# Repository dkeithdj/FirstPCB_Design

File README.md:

# First PCB Design
An attempt to create my first PCB Design

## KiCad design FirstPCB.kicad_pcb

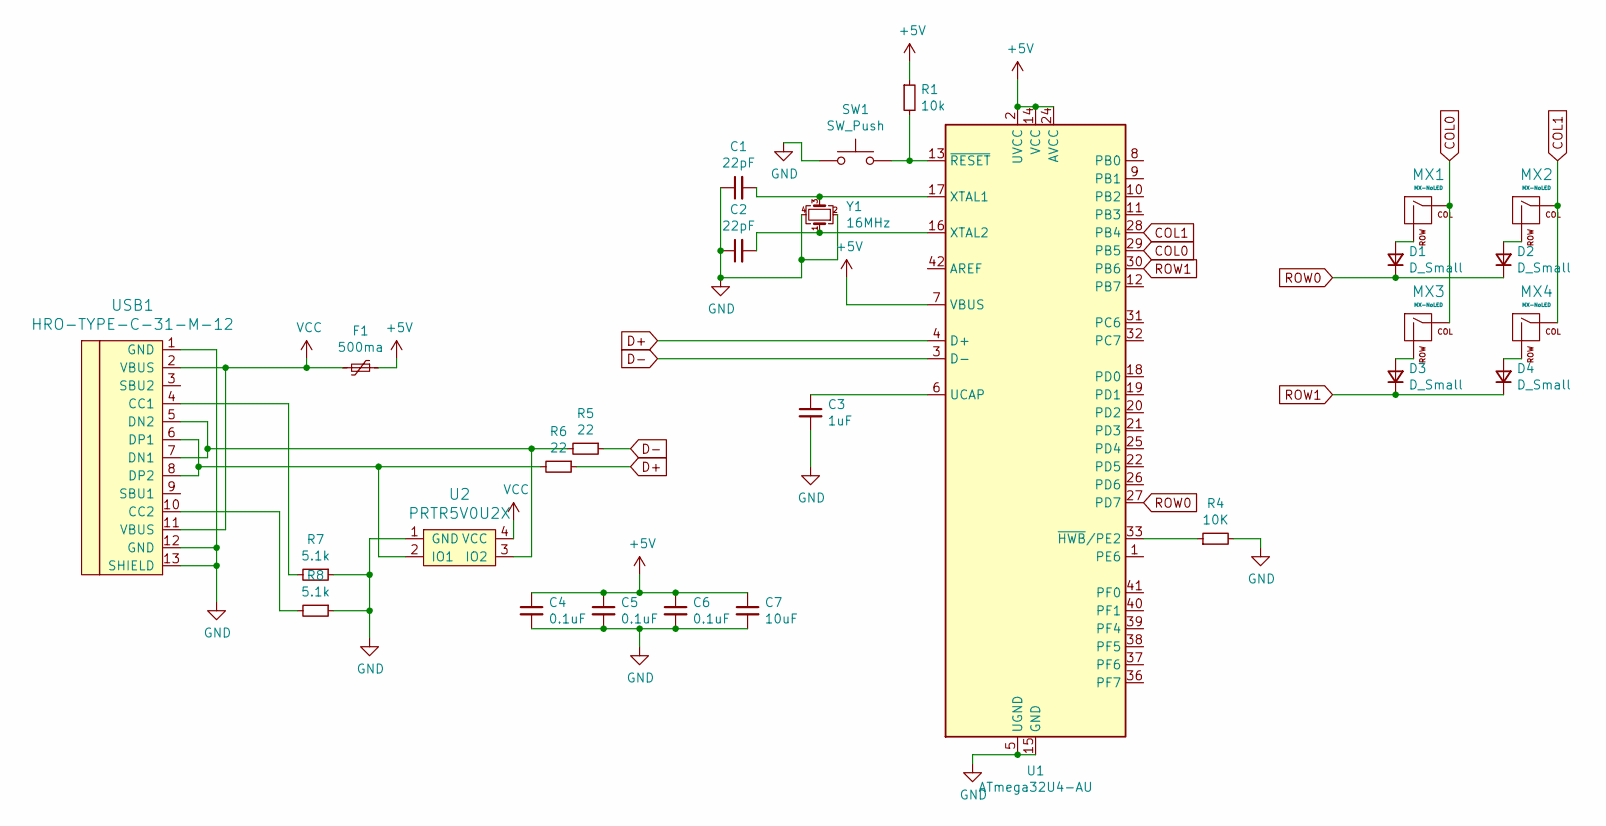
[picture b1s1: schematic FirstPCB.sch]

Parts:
C1, C2: 22pF; C_0805_2012Metric
C3: 1uF; C_0805_2012Metric
C4, C5, C6: 0.1uF; C_0805_2012Metric
C7: 10uF; C_0805_2012Metric
D1, D2, D3, D4: D_Small; D_SOD-123
F1: 500ma; Fuse_1206_3216Metric
MX1, MX2, MX3, MX4: MX-NoLED; MXOnly-1U-NoLED
R1: 10k; R_0805_2012Metric
R4: 10K; R_0805_2012Metric
R5, R6: 22; R_0805_2012Metric
R7, R8: 5.1k; R_0805_2012Metric
SW1: SW_Push; SKQG-1155865
U1: ATmega32U4-AU; TQFP-44_10x10mm_P0.8mm
U2: PRTR5V0U2X; SOT143B
USB1: HRO-TYPE-C-31-M-12; HRO-TYPE-C-31-M-12-Assembly
Y1: 16MHz; Crystal_SMD_3225-4Pin_3.2x2.5mm

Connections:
+5V: C4.1, C5.1, C6.1, C7.1, F1.1, R1.1, U1.2 (UVCC), U1.7 (VBUS), U1.14 (VCC), U1.24 (AVCC), U1.34 (VCC), U1.44 (AVCC)
COL0: MX1.1 (COL), MX3.1 (COL), U1.29 (PB5)
COL1: MX2.1 (COL), MX4.1 (COL), U1.28 (PB4)
D+: R6.1, U1.4 (D+)
D-: R5.1, U1.3 (D-)
GND: C1.1, C2.1, C3.2, C4.2, C5.2, C6.2, C7.2, R4.2, R7.1, R8.1, SW1.1, U1.5 (UGND), U1.15 (GND), U1.23 (GND), U1.35 (GND), U1.43 (GND), U2.1 (GND), USB1.1 (GND), USB1.12 (GND), USB1.13 (SHIELD), Y1.2, Y1.4
unnamed: C1.2, U1.17 (XTAL1), Y1.3
unnamed: C2.2, U1.16 (XTAL2), Y1.1
unnamed: C3.1, U1.6 (UCAP)
unnamed: D1.2 (A), MX1.2 (ROW)
unnamed: D2.2 (A), MX2.2 (ROW)
unnamed: D3.2 (A), MX3.2 (ROW)
unnamed: D4.2 (A), MX4.2 (ROW)
unnamed: R1.2, SW1.2, U1.13 (~RESET)
unnamed: R4.1, U1.33 (~HWB~/PE2)
unnamed: R5.2, U2.3 (IO2), USB1.5 (DN2), USB1.7 (DN1)
unnamed: R6.2, U2.2 (IO1), USB1.6 (DP1), USB1.8 (DP2)
unnamed: R7.2, USB1.4 (CC1)
unnamed: R8.2, USB1.10 (CC2)
ROW0: D1.1 (K), D2.1 (K), U1.27 (PD7)
ROW1: D3.1 (K), D4.1 (K), U1.30 (PB6)
VCC: F1.2, U2.4 (VCC), USB1.2 (VBUS), USB1.11 (VBUS)

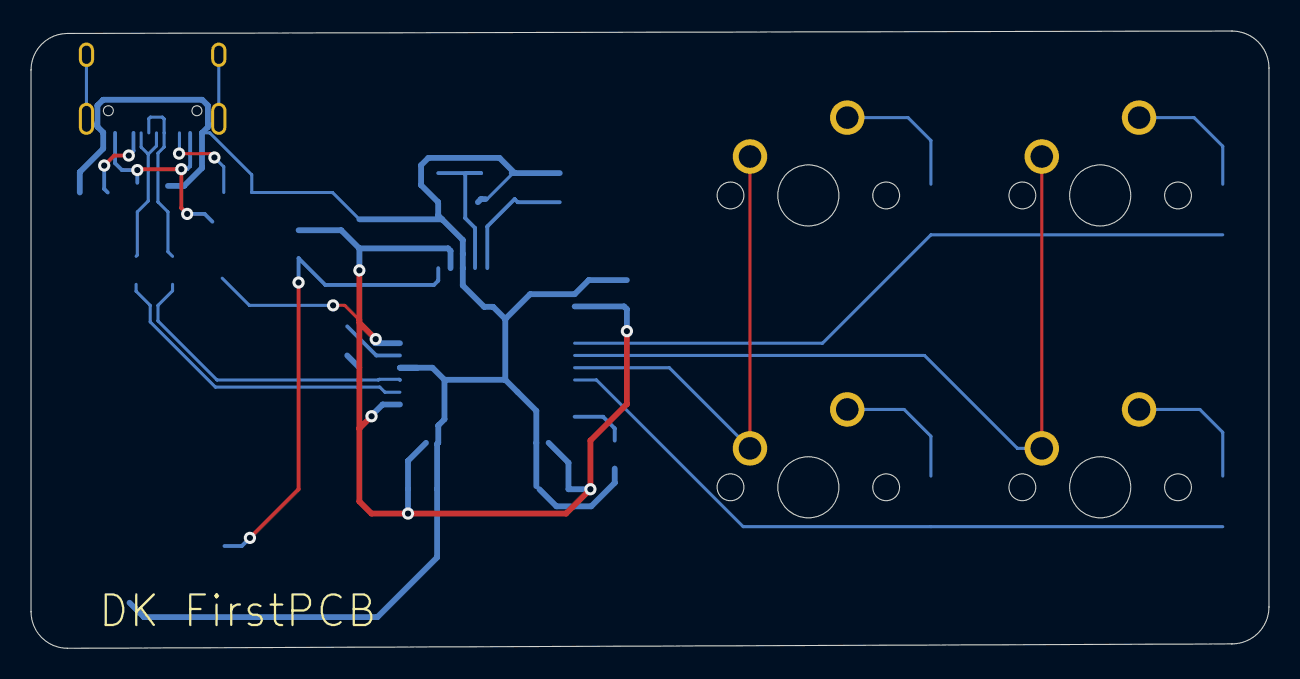
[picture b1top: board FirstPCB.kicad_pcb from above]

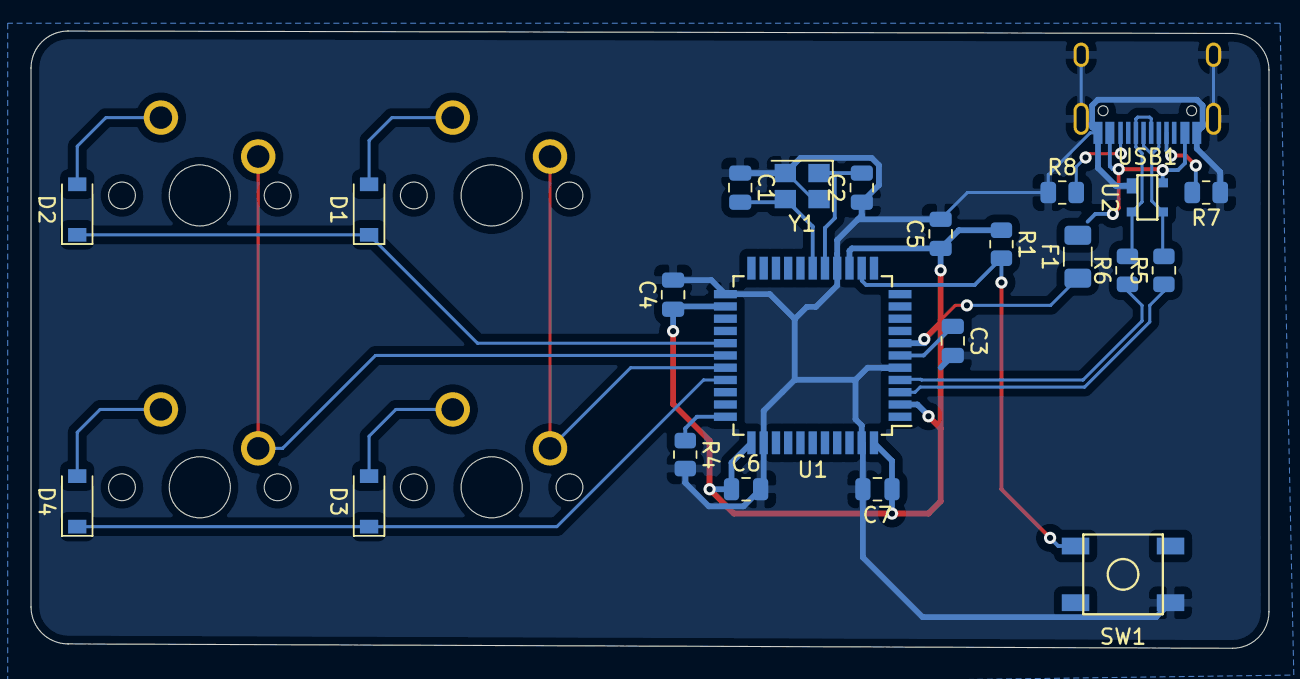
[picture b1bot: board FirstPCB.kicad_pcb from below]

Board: 2 copper layers, 80.8 x 40.3 mm, 27 parts (23 on the bottom side), 22 nets.

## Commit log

2021-05-24 adding stuff
2021-05-24 add submodules
2021-05-24 stuff
2021-06-04 Converted to USB Type-C
